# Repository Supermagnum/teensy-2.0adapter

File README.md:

# teensy-2.0adapter
Adapter board that makes it possible to easily mount a Teensy++2.0 in what you may desire..

The PCB'S frontside:
https://raw.githubusercontent.com/Supermagnum/teensy-2.0adapter/master/frontside.jpg

The PCB'S backside:
https://raw.githubusercontent.com/Supermagnum/teensy-2.0adapter/master/backside.jpg

Schematic diagram:
https://github.com/Supermagnum/teensy-2.0adapter/blob/master/teensy-adapter-schema.pdf

Parts and PCB:
https://aisler.net/p/ZNWZNCBF

BOM:
https://github.com/Supermagnum/teensy-2.0adapter/blob/master/BOM.html

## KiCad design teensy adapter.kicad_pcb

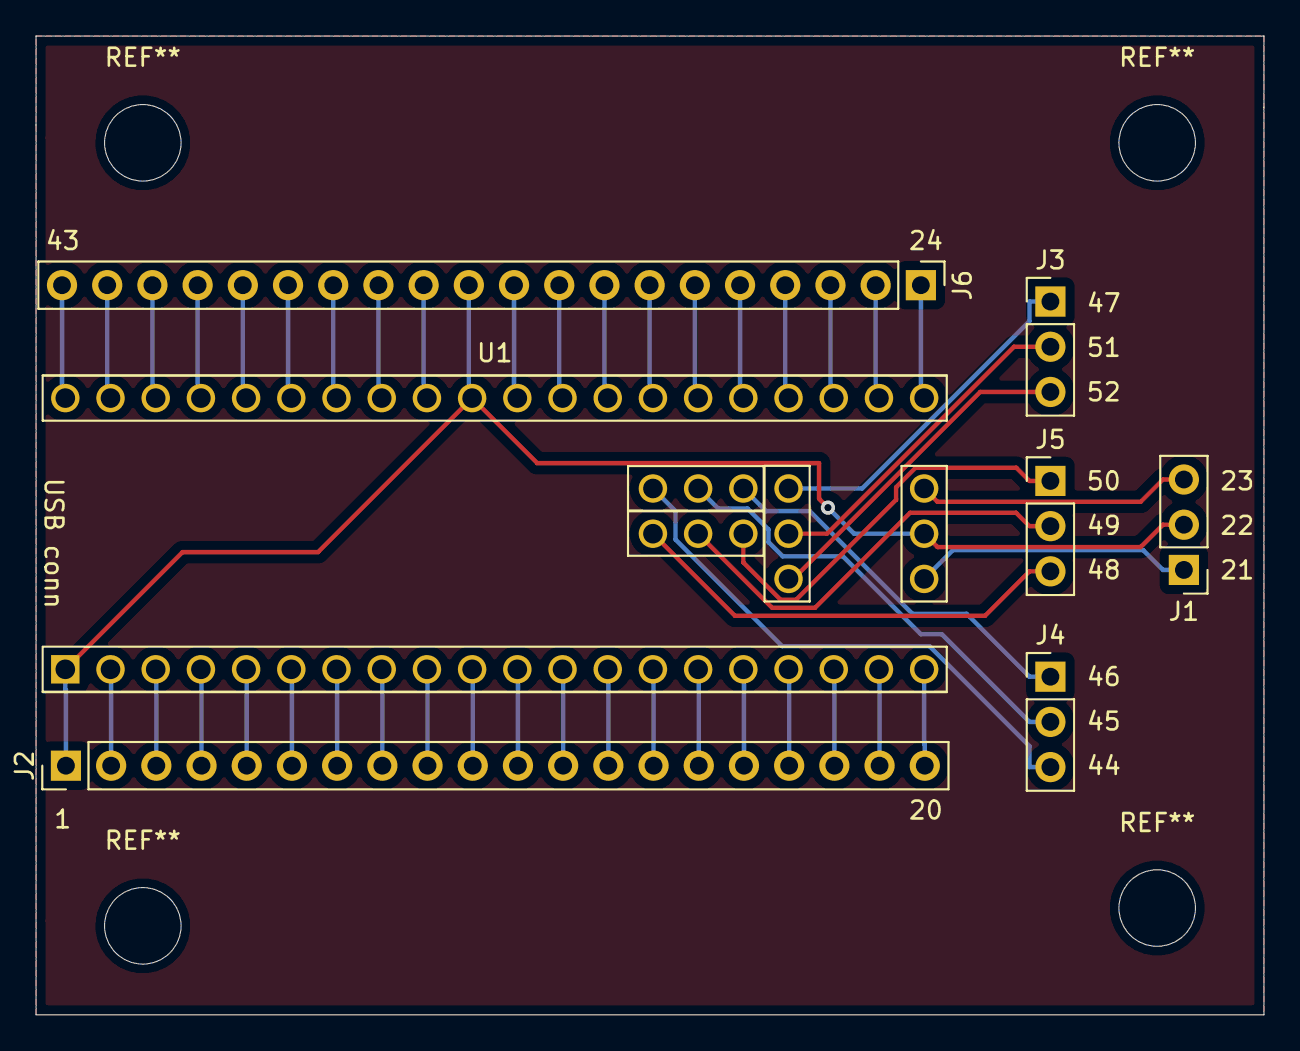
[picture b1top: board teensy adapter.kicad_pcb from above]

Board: 2 copper layers, 69.0 x 55.0 mm, 7 parts (0 on the bottom side), 50 nets.

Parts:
J1, J3, J4, J5: Conn_01x03_Female; PinHeader_1x03_P2.54mm_Vertical
J2, J6: Conn_01x20_Female; PinHeader_1x20_P2.54mm_Vertical
U1: Teensy++2.0_(Arduino); Teensy2.0-pins-headers

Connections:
/GND: J1.2, J2.1, J6.11, U1.1, U1.22, U1.34
unnamed: J1.1, U1.21
unnamed: J1.3, U1.23
unnamed: J2.2, U1.2
unnamed: J2.3, U1.3
unnamed: J2.4, U1.4
unnamed: J2.5, U1.5
unnamed: J2.6, U1.6
unnamed: J2.7, U1.7
unnamed: J2.8, U1.8
unnamed: J2.9, U1.9
unnamed: J2.10, U1.10
unnamed: J2.11, U1.11
unnamed: J2.12, U1.12
unnamed: J2.13, U1.13
unnamed: J2.14, U1.14
unnamed: J2.15, U1.15
unnamed: J2.16, U1.16
unnamed: J2.17, U1.17
unnamed: J2.18, U1.18
unnamed: J2.19, U1.19
unnamed: J2.20, U1.20
unnamed: J3.1, U1.47
unnamed: J3.2, U1.51
unnamed: J3.3, U1.52
unnamed: J4.1, U1.46
unnamed: J4.2, U1.45
unnamed: J4.3, U1.44
unnamed: J5.1, U1.50
unnamed: J5.2, U1.49
unnamed: J5.3, U1.48
unnamed: J6.1, U1.24
unnamed: J6.2, U1.25
unnamed: J6.3, U1.26
unnamed: J6.4, U1.27
unnamed: J6.5, U1.28
unnamed: J6.6, U1.29
unnamed: J6.7, U1.30
unnamed: J6.8, U1.31
unnamed: J6.9, U1.32
unnamed: J6.10, U1.33
unnamed: J6.12, U1.35
unnamed: J6.13, U1.36
unnamed: J6.14, U1.37
unnamed: J6.15, U1.38
unnamed: J6.16, U1.39
unnamed: J6.17, U1.40
unnamed: J6.18, U1.41
unnamed: J6.19, U1.42
unnamed: J6.20, U1.43

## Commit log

2020-08-28 Added files + BOM.
2020-08-29 added bom in html format
